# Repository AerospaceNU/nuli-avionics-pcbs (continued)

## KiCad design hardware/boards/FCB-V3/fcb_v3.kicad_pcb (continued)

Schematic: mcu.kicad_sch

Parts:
C5, C6, C8: 10uF; C_0603_1608Metric_Pad1.08x0.95mm_HandSolder
C9, C10, C11, C13, C21, C22, C23, C24, C26, C27, C28, C29: 100nF; C_0603_1608Metric_Pad1.08x0.95mm_HandSolder
C12: 4.7uF; C_0603_1608Metric_Pad1.08x0.95mm_HandSolder
C14, C15: 12.5p; C_0402_1005Metric
C16, C17: 10pF; C_0402_1005Metric
J1: Conn_01x05; JST_PH_B5B-PH-SM4-TB_1x05-1MP_P2.00mm_Vertical
L5: BLM18SG221TZ1D; L_0603_1608Metric_Pad1.05x0.95mm_HandSolder
U1: ATSAMD51P20A-AF; TQFP128_14X14MC_MCH
Y1: ABS06-32.768KHZ-T; XTAL_ABS06-32.768KHZ-T; PARTREV 4/25/2022
Y2: RH100-8.000-10-1010-EXT-TR; RH100_RAL

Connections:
+3V3: C5.1, C6.1, C9.1, C11.1, C21.1, C22.1, C23.1, C24.1, C26.1, C27.1, C28.1, C29.1, J1.2, L5.1, U1.32 (VDDIOB), U1.37 (VDDIOB), U1.46 (VDDIO), U1.54 (VDDIO), U1.65 (VDDIO), U1.79 (VDDIO), U1.91 (VDDIO), U1.97 (VDDIO), U1.107 (VDDIO), U1.118 (VDDIO); also elsewhere on the board
/BLE/BLE_RST: U1.36 (PA11); also elsewhere on the board
/BLE/BLE_RX: U1.21 (PA04); also elsewhere on the board
/BLE/BLE_TX: U1.22 (PA05); also elsewhere on the board
/BUZZER/BUZZER_LV_IN: U1.61 (PA13); also elsewhere on the board
/Main MCU/ADC_IN0: U1.123 (PC30); also elsewhere on the board
/Main MCU/ADC_IN1: U1.124 (PC31); also elsewhere on the board
/Main MCU/ADC_IN2: U1.125 (PB00); also elsewhere on the board
/Main MCU/ADC_IN3: U1.126 (PB01); also elsewhere on the board
/Main MCU/ADC_IN6: U1.127 (PB02); also elsewhere on the board
/Main MCU/ADC_IN7: U1.128 (PB03); also elsewhere on the board
/Main MCU/BARO1_CS: U1.20 (PB09); also elsewhere on the board
/Main MCU/FCB_SWCLK: J1.4, U1.119 (PA30)
/Main MCU/FCB_SWDIO: J1.5, U1.120 (PA31)
/Main MCU/FDCAN_RX: U1.93 (PA23); also elsewhere on the board
/Main MCU/FDCAN_TX: U1.92 (PA22); also elsewhere on the board
/Main MCU/FLASH_CS: U1.49 (PD10); also elsewhere on the board
/Main MCU/FLASH_MISO: U1.50 (PD11); also elsewhere on the board
/Main MCU/FLASH_MOSI: U1.47 (PD08); also elsewhere on the board
/Main MCU/FLASH_SCK: U1.48 (PD09); also elsewhere on the board
/Main MCU/FRAM_CS: U1.19 (PB08); also elsewhere on the board
/Main MCU/HIGH_G_CS_: U1.7 (PC02); also elsewhere on the board
/Main MCU/HIGH_G_INT: U1.8 (PC03); also elsewhere on the board
/Main MCU/IMU1_CS: U1.111 (PC27); also elsewhere on the board
/Main MCU/IMU1_INT: U1.112 (PC28); also elsewhere on the board
/Main MCU/MAG_CS: U1.9 (PA02); also elsewhere on the board
/Main MCU/MAG_INT: U1.113 (PA27); also elsewhere on the board
/Main MCU/PWM_OUT0: U1.87 (PB21); also elsewhere on the board
/Main MCU/PWM_OUT1: U1.98 (PB22); also elsewhere on the board
/Main MCU/PWM_OUT2: U1.99 (PB23); also elsewhere on the board
/Main MCU/PWM_OUT3: U1.86 (PB20); also elsewhere on the board
/Main MCU/PWM_OUT4: U1.59 (PC15); also elsewhere on the board
/Main MCU/PWM_OUT5: U1.58 (PC14); also elsewhere on the board
/Main MCU/PWM_OUT6: U1.57 (PC13); also elsewhere on the board
/Main MCU/PWM_OUT7: U1.56 (PC12); also elsewhere on the board
/Main MCU/RAD_CS: U1.33 (PA08); also elsewhere on the board
/Main MCU/RAD_IO3: U1.34 (PA09); also elsewhere on the board
/Main MCU/RAD_RST: U1.40 (PB11); also elsewhere on the board
/Main MCU/RFFE_HGM: U1.35 (PA10); also elsewhere on the board
/Main MCU/SPI1_MISO: U1.30 (PC07); also elsewhere on the board
/Main MCU/SPI1_MOSI: U1.27 (PC04); also elsewhere on the board
/Main MCU/SPI1_SCK: U1.28 (PC05); also elsewhere on the board
/Main MCU/SPI2_MISO: U1.44 (PB15); also elsewhere on the board
/Main MCU/SPI2_MOSI: U1.41 (PB12); also elsewhere on the board
/Main MCU/SPI2_SCK: U1.42 (PB13); also elsewhere on the board
/Main MCU/UART1_RX: U1.122 (PB31); also elsewhere on the board
/Main MCU/UART1_TX: U1.121 (PB30); also elsewhere on the board
/Main MCU/UART2_RX: U1.67 (PA17); also elsewhere on the board
/Main MCU/UART2_TX: U1.66 (PA16); also elsewhere on the board
/Main MCU/USB_DN: U1.94 (PA24); also elsewhere on the board
/Main MCU/USB_DP: U1.95 (PA25); also elsewhere on the board
/Main MCU/USER_LED: U1.110 (PC26); also elsewhere on the board
/Main MCU/VDDANA: C8.1, C10.1, L5.2, U1.6 (VDDANA), U1.15 (VDDANA), U1.26 (VDDANA)
/Main MCU/VDDCORE: C12.1, C13.1, U1.115 (VDDCORE)
/Main MCU/XIN32: C14.2, U1.1 (PA00), Y1.1
/Main MCU/XOUT32: C15.2, U1.2 (PA01), Y1.2
/Main MCU/nRST: J1.3, U1.114 (RESETN)
/PERIPH_EN: U1.60 (PA12); also elsewhere on the board
/Sensors/GPS_PPS: U1.10 (PA03); also elsewhere on the board
GND: C5.2, C6.2, C8.2, C9.2, C10.2, C11.2, C12.2, C13.2, C14.1, C15.1, C16.1, C17.1, C21.2, C22.2, C23.2, C24.2, C26.2, C27.2, C28.2, C29.2, J1.1, U1.5 (GND), U1.14 (GNDANA), U1.25 (GNDANA), U1.31 (GND), U1.38 (GND), U1.45 (GND), U1.53 (GND), U1.64 (GND), U1.78 (GND), U1.90 (GND), U1.96 (GND), U1.106 (GND), U1.116 (GNDIO); also elsewhere on the board

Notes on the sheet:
100 and 4.7 uF caps are decoupling. Place as close to MCU as possible.
Idk anything about which inductor to pick. Double check this.
Power
Oscillators
MCU

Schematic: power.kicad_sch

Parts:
C40, C41: 10u; C_0603_1608Metric
C42: 22u; C_0603_1608Metric
C43, C62, C63: 0.1u; C_0402_1005Metric
C44, C45: 22u; C_0805_2012Metric
D4, D6: RED; LED_0603_1608Metric
J14: Screw_Terminal_01x04; TerminalBlock_TE_282834-4_1x04_P2.54mm_Horizontal
L3: CDMT40D30HF-3R3NC
R24: 49.9k; R_0402_1005Metric
R25, R27, R30, R31: 10k; R_0402_1005Metric
R26: 34.8k; R_0402_1005Metric
R28, R33: 4.7k; R_0402_1005Metric
R29: 52.3k; R_0402_1005Metric
R32: 402R; R_0402_1005Metric
TP6: BAT+; TestPoint_Pad_4.0x4.0mm
TP8: PYRO+; TestPoint_Pad_4.0x4.0mm
TP9: PYRO-; TestPoint_Pad_4.0x4.0mm
U13: AP62301Z6-7; SOT-563
U15: TPS2115ADRBR; SON65P300X300X100-9N
U29: MCP1727-3302xMF; DFN-8-1EP_3x3mm_P0.65mm_EP1.55x2.4mm

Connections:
+3V3: C42.1, D6.2 (A), R28.2, U29.7 (Sense), U29.8 (Vout); also elsewhere on the board
+5V: C41.1, U15.7 (OUT), U29.1 (Vin), U29.2 (Vin), U29.3 (~SHDN), U29.6 (Cdelay); also elsewhere on the board
/Power Supplies/3V3_PGOOD: U29.5 (PWRGD)
/Power Supplies/BATT_5V: C44.1, C45.1, C62.2, L3.2, R29.1, R31.1, U15.3 (D1), U15.8 (IN1); also elsewhere on the board
/Power Supplies/BATT_PYRO_IN: R26.1; also elsewhere on the board
/Power Supplies/BATT_SYS_IN: C40.1, R24.1, U13.1 (VIN); also elsewhere on the board
/Power Supplies/PYRO_BATT_EXT_SW: J14.2; also elsewhere on the board
/Power Supplies/PYRO_BATT_SENSE: R26.2, R27.1; also elsewhere on the board
/Power Supplies/Peripheral Power/PERIPH_5V_PGOOD: D4.1 (K); also elsewhere on the board
/Power Supplies/SYS_BATT_EXT_SW: J14.3; also elsewhere on the board
/Power Supplies/USB_5V_IN: C63.2, U15.6 (IN2); also elsewhere on the board
/Power Supplies/VBATT_SENSE: R24.2, R25.1; also elsewhere on the board
/Power Supplies/batt_5v_LX: C43.1, L3.1, U13.2 (SW)
GND: C40.2, C41.2, C42.2, C44.2, C45.2, C62.1, C63.1, R25.2, R27.2, R30.2, R31.2, R32.1, TP9.1, U13.3 (GND), U15.2 (D0), U15.5 (GND), U15.9 (GND), U15.10 (GND), U29.4 (GND), U29.9 (GND); also elsewhere on the board
unnamed: D4.2 (A), R28.1
unnamed: D6.1 (K), R33.2
unnamed: J14.1, TP8.1
unnamed: J14.4, TP6.1
unnamed: C43.2, U13.4 (BST)
unnamed: R29.2, R30.1, U13.6 (FB)
unnamed: R32.2, U15.4 (ILIM)
unnamed: R33.1, U15.1 (STAT)

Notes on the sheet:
Place near U15
1.5A max output Route 10-12 mil width
Low ESR RMS current > 1 amp
Low ESR ceramic output caps
3.3uH >=3A saturation current <30mOhm DC resistance
I_L = 500/R_ILIM
Need to figure out 5v consumption, 3.3v consumption
6V in max, 3.3v @ 1.5A out
We want to prioritize battery, if present D[1..0]=00, out=in2 D[1..0]=10, out=in1 So D1=in1, D0=gnd, IN1=BATTERY, IN2=USB
14v in max!
5mA sink max
4.2-18v in 0.8-7v output @ 3A 750khz
Design requirements: - 3V0A output @ 50 mA (tcxo for cc1200) - 3V3 output @ 700 mA - See FCB V2 Math sheet - 3V9A output @ 1A (rffe) - 5v @ ???A for servos+cameras
Hi-Z if the IN2 switch is ON. pulls low if the IN1 switch is ON LED will be off when on USB, on when on battery
Note: can't draw past USB spec on this pin! Source straight from battery->5v if you need more than 0.5A
12.6v in max!

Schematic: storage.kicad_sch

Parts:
C46: 1u; C_0603_1608Metric
C47, C48, C49: 0.1u; C_0402_1005Metric
R34, R35, R36: 100k; R_0402_1005Metric
U17: MB85RS64PNF; SOP-8_3.76x4.96mm_P1.27mm
U18: S25FL512SAGMFA011; SOIC-16W_7.5x10.3mm_P1.27mm

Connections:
+3V3: C46.2, C47.2, C48.1, C49.2, R34.1, R35.1, R36.1, U17.8 (VDD), U18.2 (VCC), U18.14 (VCCIO/RFU); also elsewhere on the board
/Main MCU/FLASH_CS: U18.7 (nCS); also elsewhere on the board
/Main MCU/FLASH_MISO: U18.8 (SO/IO1); also elsewhere on the board
/Main MCU/FLASH_MOSI: U18.15 (SI/IO0); also elsewhere on the board
/Main MCU/FLASH_SCK: U18.16 (SCK); also elsewhere on the board
/Main MCU/FRAM_CS: U17.1 (~CS); also elsewhere on the board
/Main MCU/SPI1_MISO: U17.2 (SO); also elsewhere on the board
/Main MCU/SPI1_MOSI: U17.5 (SI); also elsewhere on the board
/Main MCU/SPI1_SCK: U17.6 (SCK); also elsewhere on the board
GND: C46.1, C47.1, C48.2, C49.1, U17.4 (GND), U18.10 (GND); also elsewhere on the board
unnamed: R35.2, U17.7 (~HOLD)
unnamed: R34.2, U17.3 (~WP)
unnamed: R36.2, U18.3 (nRESET/RFU)

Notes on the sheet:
FRAM MB85RS64PNF
VCCIO and RESET are n/c for us connected in case we swap p/ns
Datasheet doesn't specify probably good idea?

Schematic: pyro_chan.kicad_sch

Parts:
R51, R52, R56, R58: 10k; R_0402_1005Metric
R53, R54: 750; R_0402_1005Metric; LCSC C25130
R55, R57: 100k; R_0402_1005Metric
U23: SI7232DN-T1-GE3; TRANS_SI7232DN-T1-GE3

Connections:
/Main MCU/PWM_OUT0: R54.2; also elsewhere on the board
/Main MCU/PWM_OUT3: R53.2; also elsewhere on the board
/Pyros and Servos/PYRO1: R55.2, U23.7 (DRAIN1), U23.8 (DRAIN1), U23.9 (DRAIN1); also elsewhere on the board
/Pyros and Servos/PYRO2: R57.2, U23.5 (DRAIN2), U23.6 (DRAIN2), U23.10 (DRAIN2); also elsewhere on the board
/Pyros and Servos/PYRO_SENSE1: R55.1, R56.2; also elsewhere on the board
/Pyros and Servos/PYRO_SENSE2: R57.1, R58.2; also elsewhere on the board
GND: R51.1, R52.1, R56.1, R58.1, U23.1 (SOURCE1), U23.3 (SOURCE2); also elsewhere on the board
unnamed: R51.2, R53.1, U23.2 (GATE1)
unnamed: R52.2, R54.1, U23.4 (GATE2)

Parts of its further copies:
R16, R17, R21, R23: 10k; R_0402_1005Metric
R18, R19: 750; R_0402_1005Metric; LCSC C25130
R20, R22: 100k; R_0402_1005Metric
U12: SI7232DN-T1-GE3; TRANS_SI7232DN-T1-GE3

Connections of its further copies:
/Main MCU/PWM_OUT1: R18.2; also elsewhere on the board
/Main MCU/PWM_OUT2: R19.2; also elsewhere on the board
/Pyros and Servos/PYRO3: R20.2, U12.7 (DRAIN1), U12.8 (DRAIN1), U12.9 (DRAIN1); also elsewhere on the board
/Pyros and Servos/PYRO4: R22.2, U12.5 (DRAIN2), U12.6 (DRAIN2), U12.10 (DRAIN2); also elsewhere on the board
/Pyros and Servos/PYRO_SENSE3: R20.1, R21.2; also elsewhere on the board
/Pyros and Servos/PYRO_SENSE4: R22.1, R23.2; also elsewhere on the board
GND: R16.1, R17.1, R21.1, R23.1, U12.1 (SOURCE1), U12.3 (SOURCE2); also elsewhere on the board
unnamed: R16.2, R18.1, U12.2 (GATE1)
unnamed: R17.2, R19.1, U12.4 (GATE2)

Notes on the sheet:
Output at 1.145 when pyro at 12.6
I = (5v)/(10mA) = 500 Ohm at least
1mA pulldown
Pyro is at up to 12.6V

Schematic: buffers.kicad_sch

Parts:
C71, C74: 0.1u; C_0402_1005Metric
U3, U24: LMV324IDR

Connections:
+3V3: C71.1, C74.1, U3.4 (V+), U24.4 (V+); also elsewhere on the board
/Main MCU/ADC_IN0: U24.1, U24.2 (-); also elsewhere on the board
/Main MCU/ADC_IN1: U3.1, U3.2 (-); also elsewhere on the board
/Main MCU/ADC_IN2: U3.6 (-), U3.7; also elsewhere on the board
/Main MCU/ADC_IN3: U24.6 (-), U24.7; also elsewhere on the board
/Main MCU/ADC_IN6: U3.8, U3.9 (-); also elsewhere on the board
/Main MCU/ADC_IN7: U3.13 (-), U3.14; also elsewhere on the board
/Power Supplies/PYRO_BATT_SENSE: U24.5 (+); also elsewhere on the board
/Power Supplies/VBATT_SENSE: U3.10 (+); also elsewhere on the board
/Pyros and Servos/PYRO_SENSE1: U3.12 (+); also elsewhere on the board
/Pyros and Servos/PYRO_SENSE2: U3.3 (+); also elsewhere on the board
/Pyros and Servos/PYRO_SENSE3: U24.3 (+); also elsewhere on the board
/Pyros and Servos/PYRO_SENSE4: U3.5 (+); also elsewhere on the board
GND: C71.2, C74.2, U3.11 (V-), U24.11 (V-); also elsewhere on the board

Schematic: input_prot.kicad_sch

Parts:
Q2: SQJ974EP-T1_GE3; TRANS_SQJ974EP-T1_GE3
R2: 300k; R_0402_1005Metric
R3: 287k; R_0402_1005Metric
R8: 18.7k; R_0402_1005Metric
R9: 100k; R_0402_1005Metric
U25: LTC4365xTS8; TSOT-23-8

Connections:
/Power Supplies/BATT_SYS_IN: Q2.5, Q2.5_1, Q2.5_2, U25.7 (VOUT); also elsewhere on the board
/Power Supplies/SYS_BATT_EXT_SW: Q2.6, Q2.6_1, Q2.6_2, R2.2, R9.1, U25.1 (VIN); also elsewhere on the board
GND: R8.1, U25.4 (GND); also elsewhere on the board
unnamed: Q2.1, Q2.3
unnamed: Q2.2, Q2.4, U25.8 (GATE)
unnamed: R3.1, R8.2, U25.3 (OV)
unnamed: R2.1, R3.2, U25.2 (UV)
unnamed: R9.2, U25.5 (~SHDN)

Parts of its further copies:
Q3: SQJ974EP-T1_GE3; TRANS_SQJ974EP-T1_GE3
R68: 300k; R_0402_1005Metric
R69: 287k; R_0402_1005Metric
R70: 18.7k; R_0402_1005Metric
R71: 100k; R_0402_1005Metric
U26: LTC4365xTS8; TSOT-23-8

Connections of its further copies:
/Power Supplies/BATT_PYRO_IN: Q3.5, Q3.5_1, Q3.5_2, U26.7 (VOUT); also elsewhere on the board
/Power Supplies/PYRO_BATT_EXT_SW: Q3.6, Q3.6_1, Q3.6_2, R68.2, R71.1, U26.1 (VIN); also elsewhere on the board
GND: R70.1, U26.4 (GND); also elsewhere on the board
unnamed: Q3.1, Q3.3
unnamed: Q3.2, Q3.4, U26.8 (GATE)
unnamed: R69.1, R70.2, U26.3 (OV)
unnamed: R68.1, R69.2, U26.2 (UV)
unnamed: R71.2, U26.5 (~SHDN)

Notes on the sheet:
UV and OV act at 0.5v 1v UV 16v OV 3mV offset 10nA leakage
IDK how to get power to run this if we don't know if the battery's flipped -- diode? i'm lazy
UV, OV Threshold = 500mV Requires Vin>2.2v to wake up

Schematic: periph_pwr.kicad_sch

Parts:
C51: 22u; C_0603_1608Metric
C52: 10n; C_0402_1005Metric
C53: 0.1u; C_0402_1005Metric
C54: 4.7u; C_0603_1608Metric
C55, C56: 22u; C_0805_2012Metric
L4: 2.2u; SRP5030CA-2R2M
R45, R48: 100k; R_0402_1005Metric
R46: 909k; R_0402_1005Metric
R47: 0R; R_0402_1005Metric
R49: 53.6k; R_0402_1005Metric
R50: 10k; R_0402_1005Metric
U22: AOZ2261AQI-15; QFN4X4-22L_EP2_S_AOS

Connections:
/PERIPH_EN: R45.2, U22.2 (EN); also elsewhere on the board
/Power Supplies/BATT_5V: C54.2, R48.1, U22.21 (VCC); also elsewhere on the board
/Power Supplies/BATT_SYS_IN: C51.1, R46.2, U22.7 (IN), U22.8 (IN), U22.9 (IN), U22.23 (IN); also elsewhere on the board
/Power Supplies/PERIPH_5V: C55.1, C56.1, L4.2, R49.1; also elsewhere on the board
/Power Supplies/Peripheral Power/5v_PERIPH_FB: R49.2, R50.1, U22.5 (FB)
/Power Supplies/Peripheral Power/PERIPH_5V_PGOOD: R48.2, U22.1 (PGOOD); also elsewhere on the board
/Power Supplies/Peripheral Power/periph_lx: C53.2, L4.1, U22.10 (LX), U22.11 (LX), U22.16 (LX), U22.17 (LX), U22.18 (LX), U22.24 (LX)
GND: C51.2, C52.1, C54.1, C55.2, C56.2, R45.1, R47.2, R50.2, U22.4 (AGND), U22.12 (PGND), U22.13 (PGND), U22.14 (PGND), U22.15 (PGND), U22.19 (PGND); also elsewhere on the board
unnamed: R47.1, U22.3 (*PFM)
unnamed: C53.1, U22.20 (BST)
unnamed: C52.2, U22.22 (SS)
unnamed: R46.1, U22.6 (TON)

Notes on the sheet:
X5R or X7R or low ESR tantalum suggested consider swaping these to larger footprint?
Vfb=0.8v
9.7a rated, 10a sat
3.3mS soft start is this reasonable?
TODO: recalculate T_ON and R_TON @ 11.1v input, 5v output
8A output programmable frequency 4-28v input
Inductor selection https://www.digikey.com/en/products/filter/fixed-inductors/71?s=N4IgjCBcoGwJxVAYygMwIYBsDOBTANCAPZQDaIALAAxwDMdIAuoQA4AuUIAymwE4CWAOwDmIAL6EAHFUQgUkDDgLEylKgCYqtCIWpgwFAKxNWHSNz5DRE8OrAJoctFjyESkcurjqA7HZCEfhQUOiAwhlTBAWGG6hQ%2B0eEhoeGGksaE4ZJgMpkwtIYp4V6JMD5UoT5wkmXRPob1MHUNtLkg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

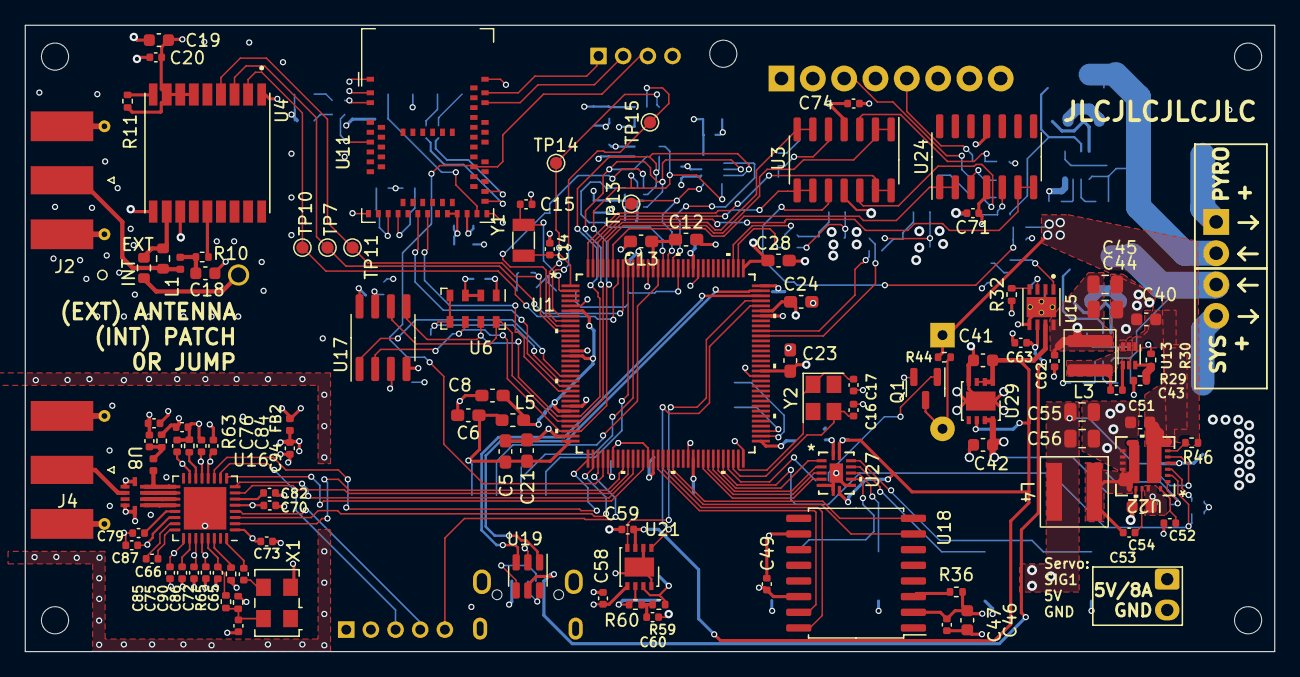
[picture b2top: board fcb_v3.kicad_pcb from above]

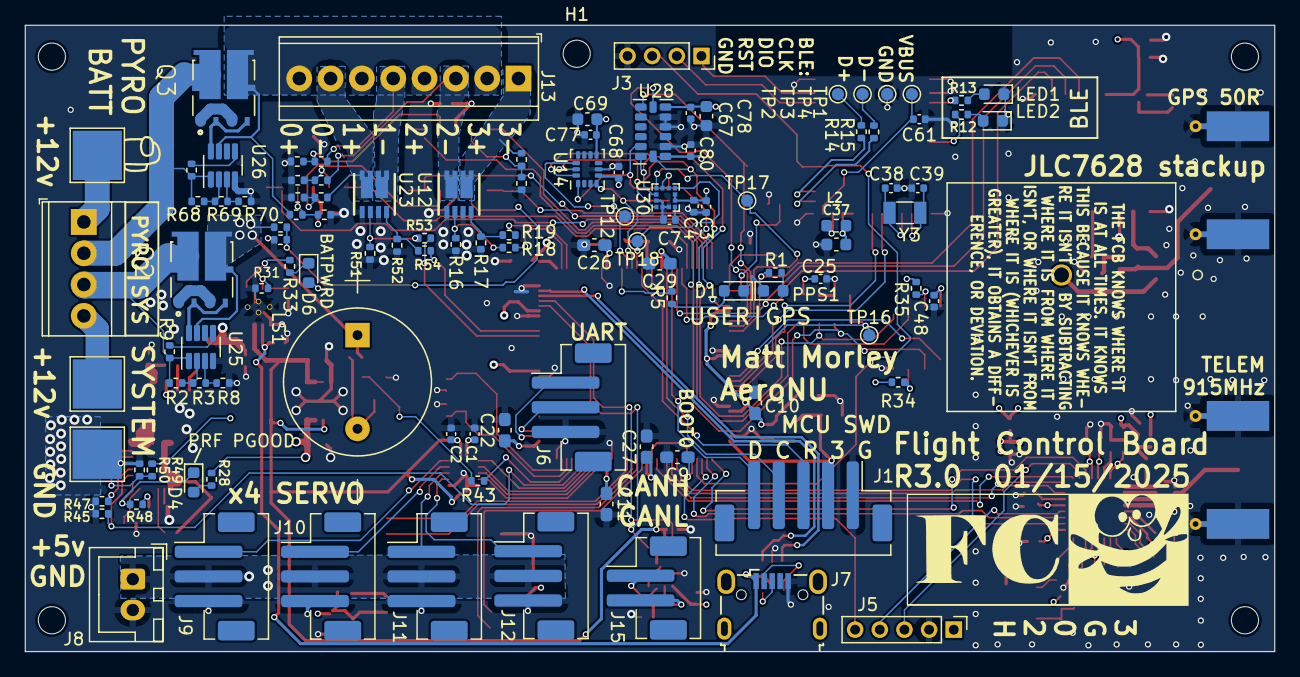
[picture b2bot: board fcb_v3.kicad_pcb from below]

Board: 4 copper layers, 101.3 x 50.8 mm, 227 parts (113 on the bottom side), 167 nets.

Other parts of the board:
D1: LED_Small; LED_0603_1608Metric
R5: 2.2k; R_0402_1005Metric

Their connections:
/Main MCU/USER_LED: R5.2; also elsewhere on the board
GND: D1.1 (K); also elsewhere on the board
unnamed: D1.2 (A), R5.1

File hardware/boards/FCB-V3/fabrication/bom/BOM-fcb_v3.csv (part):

Comment,Designator,Footprint,LCSC,Quantity
27n,L1,L_0402_1005Metric,C2041663,1
0R,R61,R_0603_1608Metric,C21189,1
10R,R10,R_0402_1005Metric,C25077,1
750,"R18,R19,R43,R53,R54",R_0402_1005Metric,C25130,5
ABS06-32.768KHZ-T,Y3,Crystal_SMD_3215-2Pin_3.2x1.5mm,C32346,1
47nF,"C70,C72,C73,C75,C76,C81,C84,C85,C86,C87,C90",C_0402_1005Metric,C913545,11
AOZ2261AQI-15,U22,QFN4X4-22L_EP2_S_AOS,,1
ATSAMD51P20A-AF,U1,TQFP128_14X14MC_MCH,,1
SQJ974EP-T1_GE3,Q3,TRANS_SQJ974EP-T1_GE3,,1
SQJ974EP-T1_GE3,Q2,TRANS_SQJ974EP-T1_GE3,,1
AO3414,Q1,SOT-23,,1
100nF,C21,C_0603_1608Metric_Pad1.08x0.95mm_HandSolder,,1
10,R64,R_0402_1005Metric,,1
0.1u,C74,C_0402_1005Metric,,1
0.1u,C71,C_0402_1005Metric,,1
MountingHole,H5,MountingHole_2.2mm_M2,,1
Conn_Coaxial,J4,SMA_Molex_73251-1153_EdgeMount_Horizontal,,1
0.1u,C59,C_0402_1005Metric,,1
100nF,C23,C_0603_1608Metric_Pad1.08x0.95mm_HandSolder,,1
12.5p,C15,C_0402_1005Metric,,1
TestPoint,TP15,TestPoint_Pad_D1.0mm,,1
LMV324IDR,U24,SOIC-14_3.9x8.7mm_P1.27mm,,1
LFD21868MMF1D386,U8,LFD21868MMF1D386_MUR,,1
10k,R30,R_0402_1005Metric,,1
TestPoint,TP13,TestPoint_Pad_D1.0mm,,1
0R,R65,R_0402_1005Metric,,1
10uF,C5,C_0603_1608Metric_Pad1.08x0.95mm_HandSolder,,1
52.3k,R29,R_0402_1005Metric,,1
0.1u,C58,C_0402_1005Metric,,1
10n,C52,C_0402_1005Metric,,1
0.1u,C49,C_0402_1005Metric,,1
220nF,C82,C_0402_1005Metric,,1
0.1u,C20,C_0402_1005Metric,,1
33p,C89,C_0402_1005Metric,,1
100nF,C24,C_0603_1608Metric_Pad1.08x0.95mm_HandSolder,,1
MAX-M10S-00B,U4,XCVR_MAX-M8C-0-10,,1
RH100-8.000-10-1010-EXT-TR,Y2,Crystal_SMD_3225-4Pin_3.2x2.5mm,,1
22u,C55,C_0805_2012Metric,,1
CDMT40D30HF-3R3NC,L3,CDMT40D30HF-3R3NC,,1
LMV324IDR,U3,SOIC-14_3.9x8.7mm_P1.27mm,,1
22u,C51,C_0603_1608Metric,,1
100nF,C28,C_0603_1608Metric_Pad1.08x0.95mm_HandSolder,,1
1.5k,R66,R_0402_1005Metric,,1
0.1uF,C64,C_0402_1005Metric,,1
56k,R63,R_0402_1005Metric,,1
0.1u,C47,C_0402_1005Metric,,1
12.5p,C14,C_0402_1005Metric,,1
4.7uF,C12,C_0603_1608Metric_Pad1.08x0.95mm_HandSolder,,1
100nF,C13,C_0603_1608Metric_Pad1.08x0.95mm_HandSolder,,1
10uF,C8,C_0603_1608Metric_Pad1.08x0.95mm_HandSolder,,1
BLM15AG102SN1D,FB2,L_0402_1005Metric,,1
1k,R44,R_0402_1005Metric,,1
MB85RS64PNF,U17,SOP-8_3.76x4.96mm_P1.27mm,,1
60R 1%,R59,R_0402_1005Metric,,1
10pF,C16,C_0402_1005Metric,,1
10u,C18,C_0603_1608Metric,,1
10uF,C6,C_0603_1608Metric_Pad1.08x0.95mm_HandSolder,,1
0.1u,C62,C_0402_1005Metric,,1
DNP,R62,R_0603_1608Metric,,1
0.1u,C53,C_0402_1005Metric,,1
MountingHole,H2,MountingHole_2.2mm_M2,,1
TestPoint,TP10,TestPoint_Pad_D1.0mm,,1
22u,C56,C_0805_2012Metric,,1
S25FL512SAGMFA011,U18,SOIC-16W_7.5x10.3mm_P1.27mm,,1
10u,C19,C_0603_1608Metric,,1
TestPoint,TP11,TestPoint_Pad_D1.0mm,,1
TPS2115ADRBR,U15,SON65P300X300X100-9N,,1
100k,R11,R_0402_1005Metric,,1
2.2u,C94,C_0402_1005Metric,,1
8.2n,L10,L_0402_1005Metric,,1
0.1u,C43,C_0402_1005Metric,,1
MS5607-02BA,U6,LGA-8_3x5mm_P1.25mm,,1
MountingHole,H4,MountingHole_2.2mm_M2,,1
0.1u,C63,C_0402_1005Metric,,1
10u,C40,C_0603_1608Metric,,1
22u,C45,C_0805_2012Metric,,1
TXU0104BQAR,U27,U_TXU0104_TEX,,1
22u,C44,C_0805_2012Metric,,1
TXETBlSANF-40.000,X1,Oscillator_SMD_TXC_7C-4Pin_5.0x3.2mm,,1
MDBT50Q-1MV2,U11,Raytac_MDBT50Q,,1
100k,R36,R_0402_1005Metric,,1
402R,R32,R_0402_1005Metric,,1
1u,C46,C_0603_1608Metric,,1
22u,C42,C_0603_1608Metric,,1
60R 1%,R60,R_0402_1005Metric,,1
32.768 kHz,Y1,Crystal_SMD_3215-2Pin_3.2x1.5mm,,1
1.5nF,C66,C_0402_1005Metric,,1
AP62301Z6-7,U13,SOT-563,,1
MCP1727-3302xMF,U29,DFN-8-1EP_3x3mm_P0.65mm_EP1.55x2.4mm,,1
10nF,C91,C_0402_1005Metric,,1
10u,C41,C_0603_1608Metric,,1
TestPoint,TP7,TestPoint_Pad_D1.0mm,,1
2.2u,L4,SRP5030CA-2R2M,,1
USBLC6-2SC6,U19,SOT-23-6,,1
Conn_Coaxial,J2,SMA_Molex_73251-1153_EdgeMount_Horizontal,,1
909k,R46,R_0402_1005Metric,,1
100pF,C93,C_0402_1005Metric,,1
10pF,C17,C_0402_1005Metric,,1
MountingHole,H3,MountingHole_2.2mm_M2,,1
0.1u,C60,C_0402_1005Metric,,1
CC1200,U16,QFN-32-1EP_5x5mm_P0.5mm_EP3.45x3.45mm,,1
DNM,R67,R_0402_1005Metric,,1
10nF,C79,C_0402_1005Metric,,1
BLM18SG221TZ1D,L5,L_0603_1608Metric_Pad1.05x0.95mm_HandSolder,,1
TJA1042TK-3,U21,DFN-8-1EP_3x3mm_P0.65mm_EP1.55x2.4mm,,1
TestPoint,TP14,TestPoint_Pad_D1.0mm,,1
4.7u,C54,C_0603_1608Metric,,1
22p,C65,C_0402_1005Metric,,1
100nF,C27,C_0603_1608Metric_Pad1.08x0.95mm_HandSolder,,1
0.1u,C25,C_0402_1005Metric,,1
100k,R35,R_0402_1005Metric,,1
10k,R17,R_0402_1005Metric,,1
DNP,L2,L_0603_1608Metric,,1
100nF,C26,C_0603_1608Metric_Pad1.08x0.95mm_HandSolder,,1
Conn_01x02,J8,JST_XH_B2B-XH-A_1x02_P2.50mm_Vertical,,1
TestPoint,TP1,TestPoint_Pad_D1.0mm,,1
100nF,C11,C_0603_1608Metric_Pad1.08x0.95mm_HandSolder,,1
TestPoint,TP16,TestPoint_Pad_D1.0mm,,1
10k,R23,R_0402_1005Metric,,1
10k,R25,R_0402_1005Metric,,1
100k,R45,R_0402_1005Metric,,1
0R,R47,R_0402_1005Metric,,1
100k,R9,R_0402_1005Metric,,1
BAT+,TP6,TestPoint_Pad_4.0x4.0mm,,1
287k,R3,R_0402_1005Metric,,1
LED_Small,LED1,LED_0603_1608Metric,,1
ADXL375,U28,LGA-14_3x5mm_P0.8mm_LayoutBorder1x6y,,1
15p,C39,C_0402_1005Metric,,1
15p,C38,C_0402_1005Metric,,1
100k,R57,R_0402_1005Metric,,1
Screw_Terminal_01x08,J13,TerminalBlock_TE_282834-8_1x08_P2.54mm_Horizontal,,1
PYRO+,TP8,TestPoint_Pad_4.0x4.0mm,,1
100k,R22,R_0402_1005Metric,,1
Screw_Terminal_01x04,J14,TerminalBlock_TE_282834-4_1x04_P2.54mm_Horizontal,,1
10k,R27,R_0402_1005Metric,,1
Conn_01x04_Female,J3,PinSocket_1x04_P2.00mm_Vertical,,1
10u,C61,C_0402_1005Metric,,1
MountingHole,H1,MountingHole_2.2mm_M2,,1
10n,C68,C_0402_1005Metric,,1
TestPoint,TP2,TestPoint_Pad_D1.0mm,,1
LTC4365xTS8,U25,TSOT-23-8,,1
100k,R48,R_0402_1005Metric,,1
LED_Small,D1,LED_0603_1608Metric,,1
300k,R2,R_0402_1005Metric,,1
Antenna,AE1,CGGBP.18.4.A.02,,1
10u,C78,C_0603_1608Metric,,1
SI7232DN-T1-GE3,U12,TRANS_SI7232DN-T1-GE3,,1
RED,D4,LED_0603_1608Metric,,1
0.1u,C77,C_0402_1005Metric,,1
300k,R68,R_0402_1005Metric,,1
CUI_CMI-1295-0585T,LS1,CUI_CMI-1295-0585T,,1
10k,R51,R_0402_1005Metric,,1
4.7k,R33,R_0402_1005Metric,,1
10k,R50,R_0402_1005Metric,,1
10k,R58,R_0402_1005Metric,,1
0.1u,C67,C_0402_1005Metric,,1
2.2u,C69,C_0603_1608Metric,,1
0.1u,C2,C_0402_1005Metric,,1
USB_B_Micro,J7,USB_Micro-B_Wuerth_629105150521,,1
27R,R14,R_0402_1005Metric,,1
0.1u,C7,C_0402_1005Metric,,1
53.6k,R49,R_0402_1005Metric,,1
10k,R52,R_0402_1005Metric,,1
10k,R56,R_0402_1005Metric,,1
100k,R20,R_0402_1005Metric,,1
287k,R69,R_0402_1005Metric,,1
2.2k,R5,R_0402_1005Metric,,1
18.7k,R8,R_0402_1005Metric,,1
10k,R21,R_0402_1005Metric,,1
TestPoint,TP4,TestPoint_Pad_D1.0mm,,1
100k,R55,R_0402_1005Metric,,1
RED,D6,LED_0603_1608Metric,,1
LIS3MDL,U30,LGA-12_2x2mm_P0.5mm,,1
0.1u,C80,C_0402_1005Metric,,1
Conn_01x03,J9,JST_PH_B3B-PH-SM4-TB_1x03-1MP_P2.00mm_Vertical,,1
100k,R71,R_0402_1005Metric,,1
100nF,C9,C_0603_1608Metric_Pad1.08x0.95mm_HandSolder,,1
TestPoint,TP12,TestPoint_Pad_D1.0mm,,1
10k,R16,R_0402_1005Metric,,1
SI7232DN-T1-GE3,U23,TRANS_SI7232DN-T1-GE3,,1
2.2k,R1,R_0402_1005Metric,,1
Conn_01x02,J15,JST_PH_B2B-PH-SM4-TB_1x02-1MP_P2.00mm_Vertical,,1
Conn_01x05,J5,PinHeader_1x05_P2.00mm_Vertical,,1
TestPoint,TP3,TestPoint_Pad_D1.0mm,,1
TestPoint,TP18,TestPoint_Pad_D1.0mm,,1
0.1u,C3,C_0402_1005Metric,,1
LTC4365xTS8,U26,TSOT-23-8,,1
TestPoint,TP17,TestPoint_Pad_D1.0mm,,1
PYRO-,TP9,TestPoint_Pad_4.0x4.0mm,,1
100k,R34,R_0402_1005Metric,,1
Conn_01x03,J10,JST_PH_B3B-PH-SM4-TB_1x03-1MP_P2.00mm_Vertical,,1
100nF,C29,C_0603_1608Metric_Pad1.08x0.95mm_HandSolder,,1
18.7k,R70,R_0402_1005Metric,,1
0.1u,C1,C_0402_1005Metric,,1
27R,R15,R_0402_1005Metric,,1
Conn_01x03,J6,JST_PH_B3B-PH-SM4-TB_1x03-1MP_P2.00mm_Vertical,,1
LED_Small,LED2,LED_0603_1608Metric,,1
1k,R13,R_0402_1005Metric,,1
49.9k,R24,R_0402_1005Metric,,1
ICM-42688-P,U14,LGA-14_3x2.5mm_P0.5mm_LayoutBorder3x4y,,1
1k,R12,R_0402_1005Metric,,1
0.1u,C48,C_0402_1005Metric,,1
34.8k,R26,R_0402_1005Metric,,1
4.7k,R28,R_0402_1005Metric,,1
10k,R31,R_0402_1005Metric,,1
1u,C4,C_0402_1005Metric,,1
100nF,C22,C_0603_1608Metric_Pad1.08x0.95mm_HandSolder,,1
10u,C37,C_0603_1608Metric,,1
Conn_01x03,J11,JST_PH_B3B-PH-SM4-TB_1x03-1MP_P2.00mm_Vertical,,1
Conn_01x05,J1,JST_PH_B5B-PH-SM4-TB_1x05-1MP_P2.00mm_Vertical,,1
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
